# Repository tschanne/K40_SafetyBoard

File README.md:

# K40_SafetyBoard" 

Board to control the laser tube, air assist, point and level indicators.
Laser can only be enabled if door is closed and water temperature is ok.
Point and level indicators brithness (LED laser diodes) can be adjusted.

Connectors: 
* J1 - air assist switch
* J2 - point indicator switch
* J3 - level indicator switch
* J4 - input screw terminal
  * pin 1: 12V
  * pin 2: 5V
  * pin 3: GND
* J5 - laser heade output
  * pin 1: air assist outout (12V)
  * pin 3: point indicator output (5V, adjustable)
  * pin 5: level indicator output (5V, adjustable)
  * pin 2,4,6: GND
* J6 - door swith connector
* J7 - water coolant sensor switch (w. jumper to deactivate)
* J8 - spare sensor switch (w. jumper to deactivate)
* J9 - PSU fire output (closed when laser enabled)
* J10 - closed when laser off
* J11 - closed when laser can be switched on

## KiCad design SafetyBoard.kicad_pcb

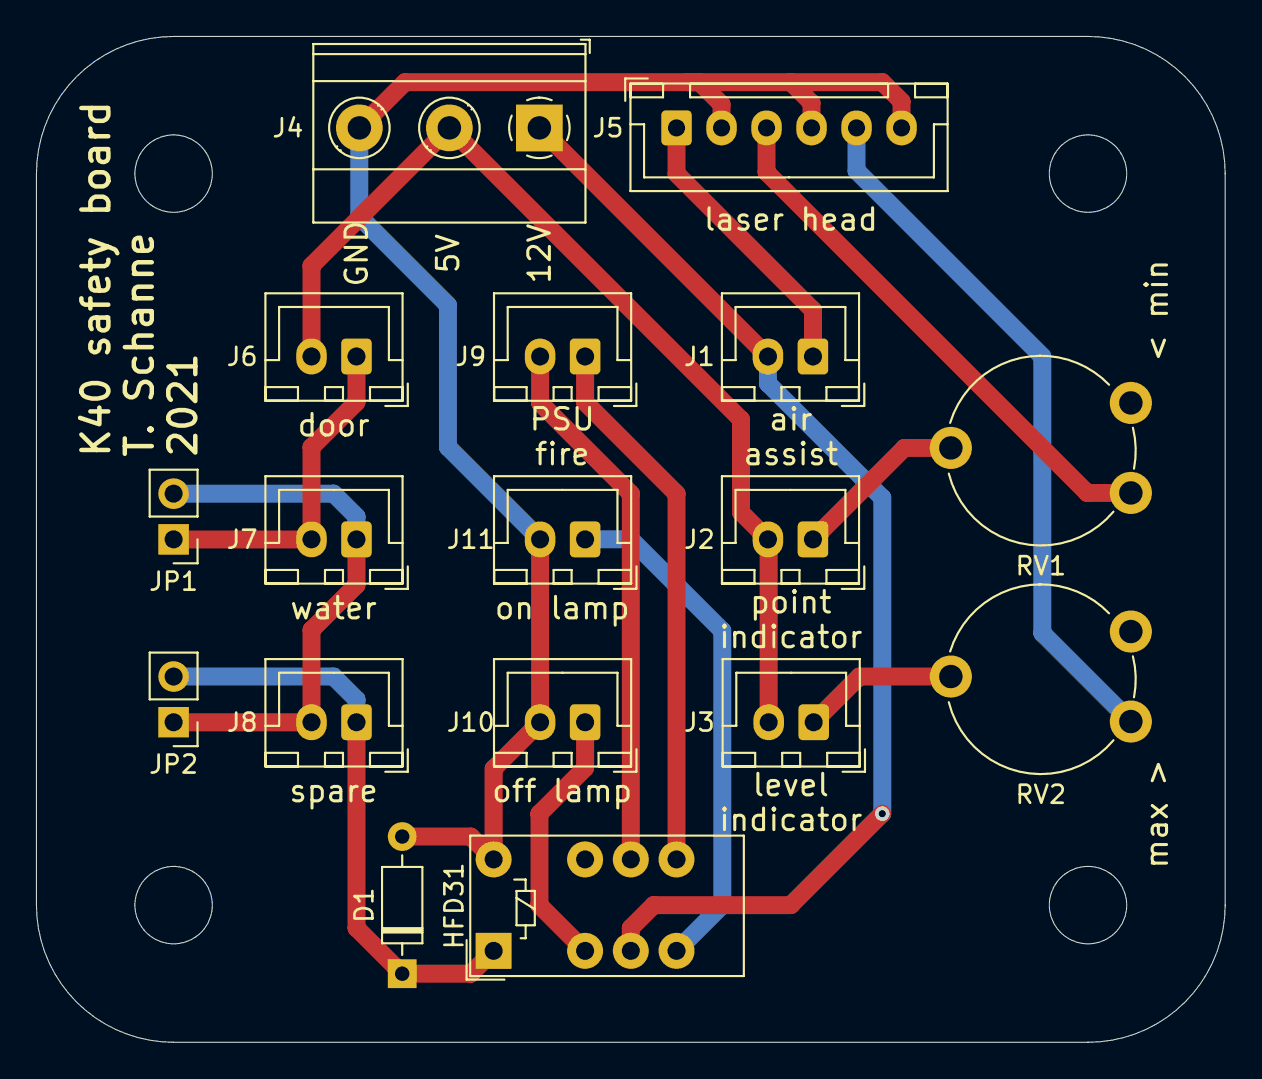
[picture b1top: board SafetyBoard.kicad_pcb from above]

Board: 2 copper layers, 66.0 x 55.9 mm, 17 parts (0 on the bottom side), 15 nets.

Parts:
D1: 1N4148; D_DO-35_SOD27_P7.62mm_Horizontal
HFD31: HFD3; Relay_HongfaHFD3
J1, J2, J3, J6, J7, J8, J9, J10, J11: Conn_01x02; JST_XH_B2B-XH-A_1x02_P2.50mm_Vertical
J4: Screw_Terminal_01x03; TerminalBlock_Phoenix_MKDS-1,5-3_1x03_P5.00mm_Horizontal
J5: Conn_01x06; JST_XH_B6B-XH-A_1x06_P2.50mm_Vertical
JP1, JP2: Jumper_2_Open; PinHeader_1x02_P2.54mm_Vertical
RV1, RV2: R_POT; Potentiometer_Piher_PT-10-V10_Vertical

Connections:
unnamed: D1.1, HFD31.1, J8.1, JP2.2
unnamed: D1.2, HFD31.12, J4.3, J5.2, J5.4, J5.6, J10.2, J11.2
unnamed: HFD31.3, J10.1
unnamed: HFD31.4, J1.2, J4.1
unnamed: HFD31.5, J11.1
unnamed: HFD31.8, J9.1
unnamed: HFD31.9, J9.2
unnamed: J1.1, J5.1
unnamed: J2.1, RV1.2
unnamed: J2.2, J3.2, J4.2, J6.2
unnamed: J3.1, RV2.2
unnamed: J5.3, RV1.3
unnamed: J5.5, RV2.3
unnamed: J6.1, J7.2, JP1.1
unnamed: J7.1, J8.2, JP1.2, JP2.1
